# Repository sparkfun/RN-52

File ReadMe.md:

SparkFun RN-52 Audio Bluetooth Breakout
=======================================

[*SparkFun RN-52 Breakout (WRL-12849)*](https://www.sparkfun.com/products/12849)

This RN-52 Bluetooth from Roving Network is an audio module that provides a highly integrated solution for delivering high quality stereo audio in a small form factor with little difficulty.

Repository Contents
-------------------
* **/Hardware** - Eagle PCB layout files
* **/Production** - Test bed files and production panel files

Product Versions
----------------
* [WRL-12849](https://www.sparkfun.com/products/12849)- Version 1.1. Currently for sale. 
* [WRL-11777](https://www.sparkfun.com/products/retired/11777)- Version 1.0. Retired. 

Version History
---------------
* [v11](https://github.com/sparkfun/RN-52/tree/V_11) GitHub version 1.1. Current version. 
* [v10](https://github.com/sparkfun/RN-52/tree/V_10) GitHub version 1.0. Retired.

License Information
-------------------
The hardware is released under [Creative Commons ShareAlike 4.0 International](https://creativecommons.org/licenses/by-sa/4.0/).

Distributed as-is; no warranty is given.

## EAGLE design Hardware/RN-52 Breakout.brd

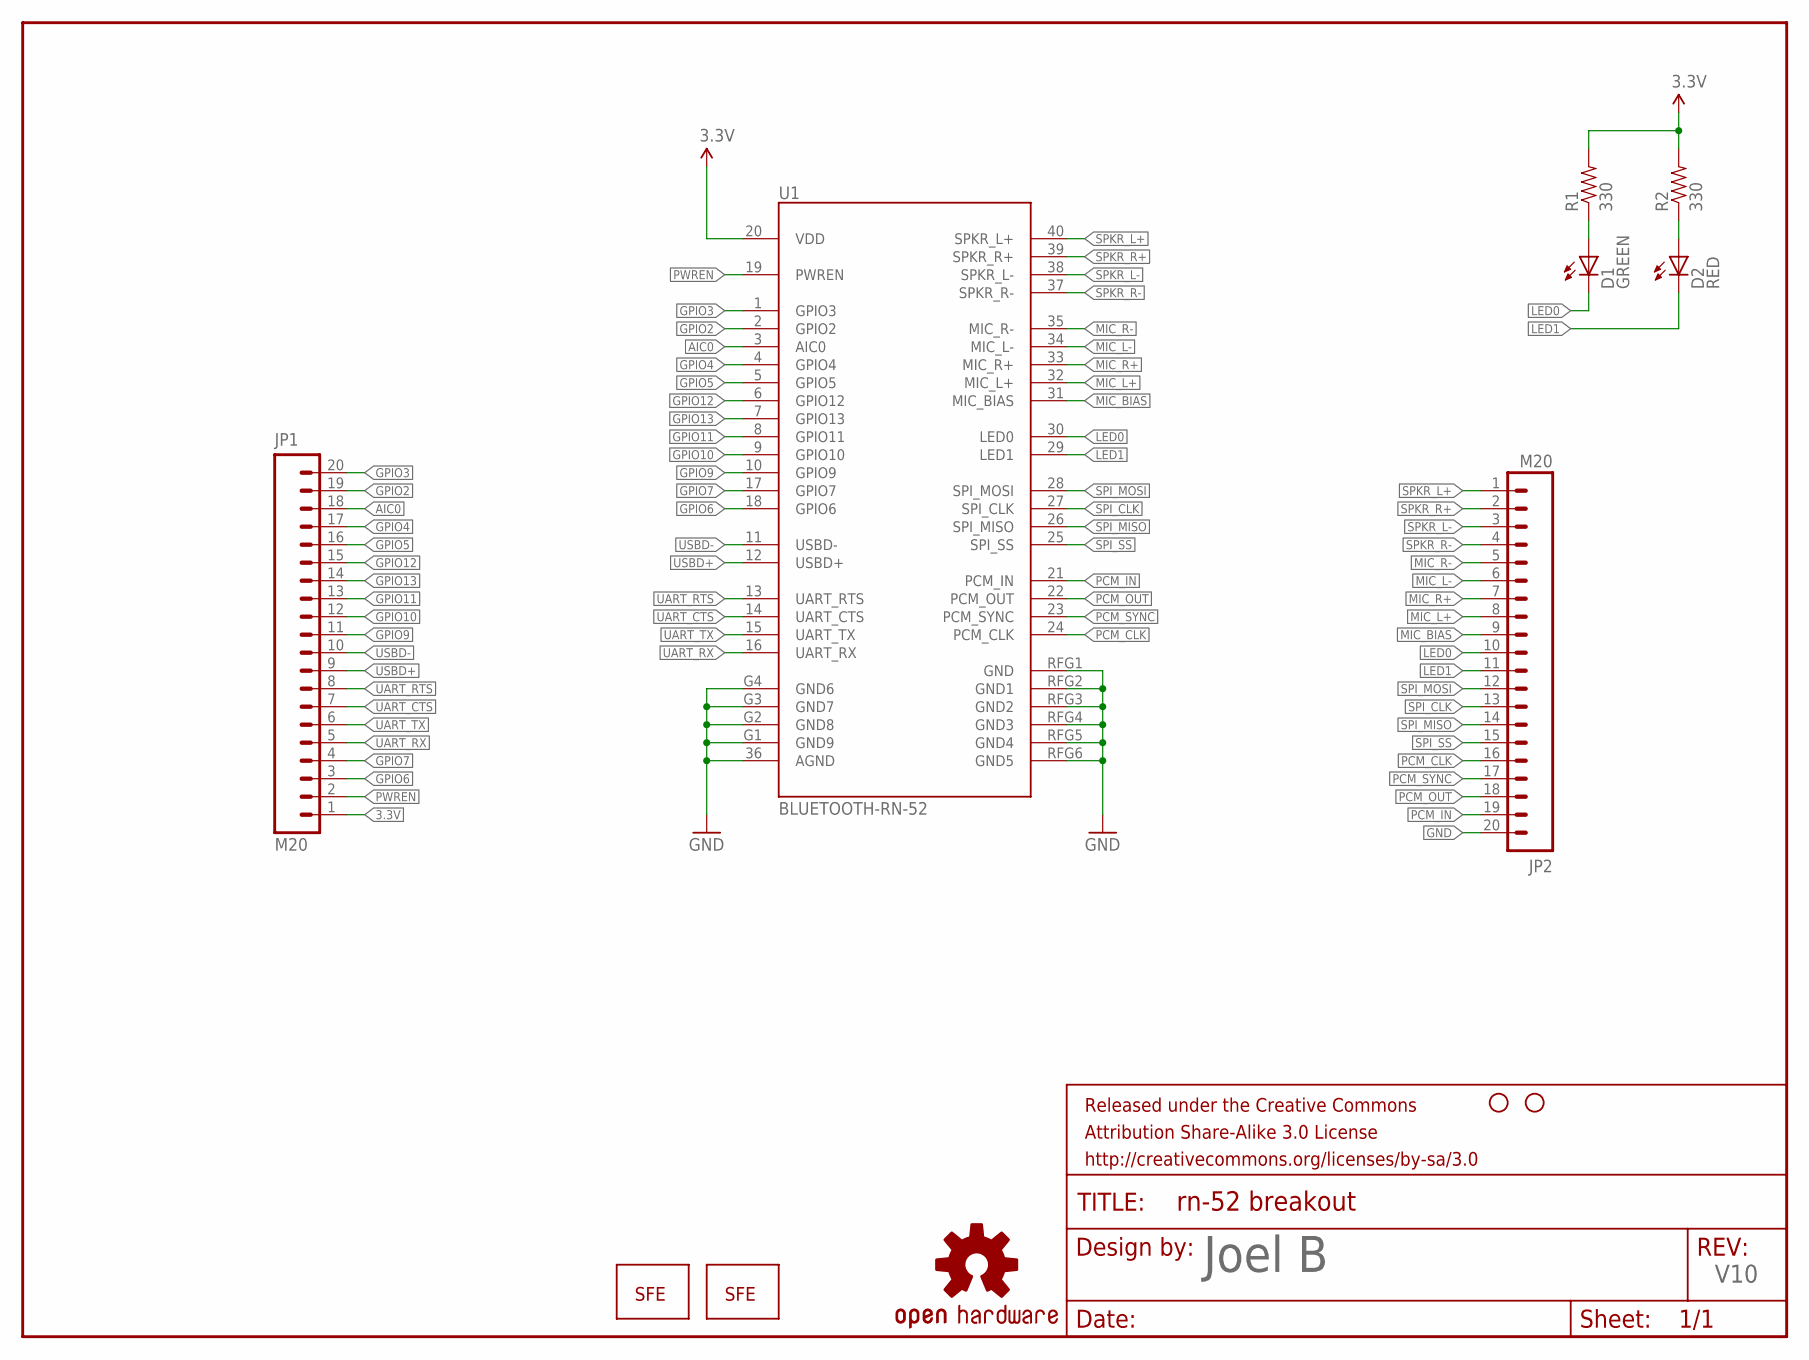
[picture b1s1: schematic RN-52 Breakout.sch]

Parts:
D1: GREEN; LED-0603
D2: RED; LED-0603
FRAME1: FRAME-LETTER; CREATIVE_COMMONS
JP1, JP2: M20; 1X20
LOGO1: OSHW-LOGOS; OSHW-LOGO-S
LOGO3: LOGO-SFENEW; SFE-NEW-WEBLOGO
LOGO4: LOGO-SFENW2; SFE-NEW-WEB
R1, R2: 330; 0603-RES
STANDOFF1, STANDOFF2: STAND-OFF
U1: BLUETOOTH-RN-52; RN-52

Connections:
3.3V: JP1.1, R1.2, R2.2, U1.20 (VDD)
AIC0: JP1.18, U1.3 (AIC0)
GND: JP2.20, U1.36 (AGND), U1.G1 (GND9), U1.G2 (GND8), U1.G3 (GND7), U1.G4 (GND6), U1.RFG1 (GND), U1.RFG2 (GND1), U1.RFG3 (GND2), U1.RFG4 (GND3), U1.RFG5 (GND4), U1.RFG6 (GND5)
GPIO2: JP1.19, U1.2 (GPIO2)
GPIO3: JP1.20, U1.1 (GPIO3)
GPIO4: JP1.17, U1.4 (GPIO4)
GPIO5: JP1.16, U1.5 (GPIO5)
GPIO6: JP1.3, U1.18 (GPIO6)
GPIO7: JP1.4, U1.17 (GPIO7)
GPIO9: JP1.11, U1.10 (GPIO9)
GPIO10: JP1.12, U1.9 (GPIO10)
GPIO11: JP1.13, U1.8 (GPIO11)
GPIO12: JP1.15, U1.6 (GPIO12)
GPIO13: JP1.14, U1.7 (GPIO13)
LED0: D1.C, JP2.10, U1.30 (LED0)
LED1: D2.C, JP2.11, U1.29 (LED1)
MIC_BIAS: JP2.9, U1.31 (MIC_BIAS)
MIC_L+: JP2.8, U1.32 (MIC_L+)
MIC_L-: JP2.6, U1.34 (MIC_L-)
MIC_R+: JP2.7, U1.33 (MIC_R+)
MIC_R-: JP2.5, U1.35 (MIC_R-)
unnamed: D2.A, R2.1
unnamed: D1.A, R1.1
PCM_CLK: JP2.16, U1.24 (PCM_CLK)
PCM_IN: JP2.19, U1.21 (PCM_IN)
PCM_OUT: JP2.18, U1.22 (PCM_OUT)
PCM_SYNC: JP2.17, U1.23 (PCM_SYNC)
PWREN: JP1.2, U1.19 (PWREN)
SPI_CLK: JP2.13, U1.27 (SPI_CLK)
SPI_MISO: JP2.14, U1.26 (SPI_MISO)
SPI_MOSI: JP2.12, U1.28 (SPI_MOSI)
SPI_SS: JP2.15, U1.25 (SPI_SS)
SPKR_L+: JP2.1, U1.40 (SPKR_L+)
SPKR_L-: JP2.3, U1.38 (SPKR_L-)
SPKR_R+: JP2.2, U1.39 (SPKR_R+)
SPKR_R-: JP2.4, U1.37 (SPKR_R-)
UART_CTS: JP1.7, U1.14 (UART_CTS)
UART_RTS: JP1.8, U1.13 (UART_RTS)
UART_RX: JP1.5, U1.16 (UART_RX)
UART_TX: JP1.6, U1.15 (UART_TX)
USBD+: JP1.9, U1.12 (USBD+)
USBD-: JP1.10, U1.11 (USBD-)

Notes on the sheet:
Joel B
V10

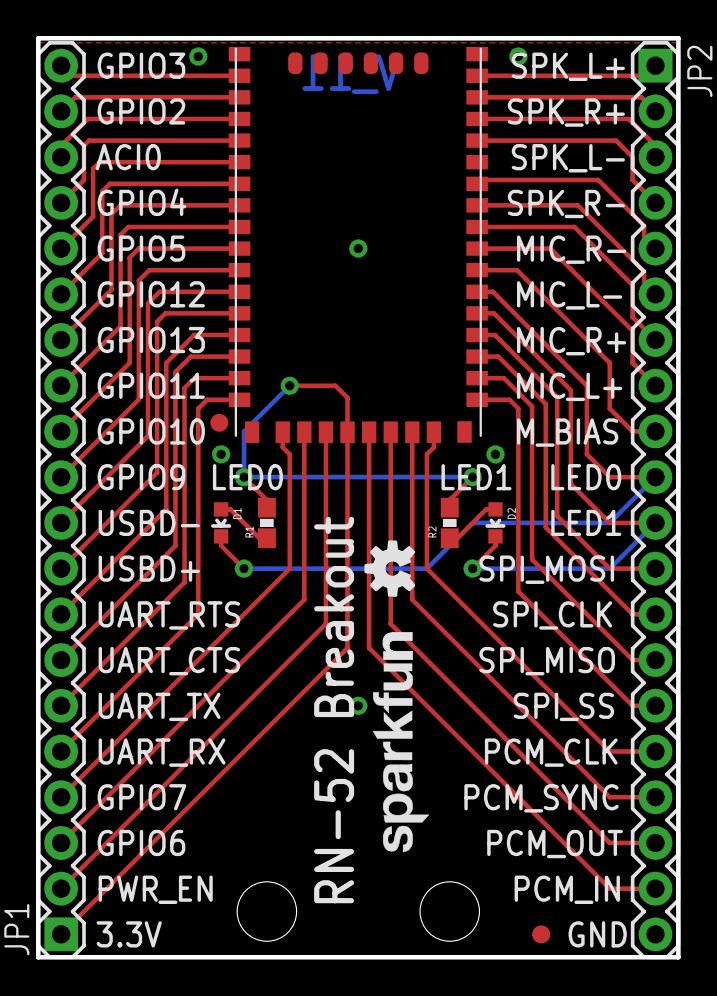
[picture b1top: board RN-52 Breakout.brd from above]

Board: 2 copper layers, 35.6 x 51.1 mm, 15 parts (1 on the bottom side), 42 nets.

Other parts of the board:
FID1, FID2: FIDUCIAL1X2; FIDUCIAL-1X2

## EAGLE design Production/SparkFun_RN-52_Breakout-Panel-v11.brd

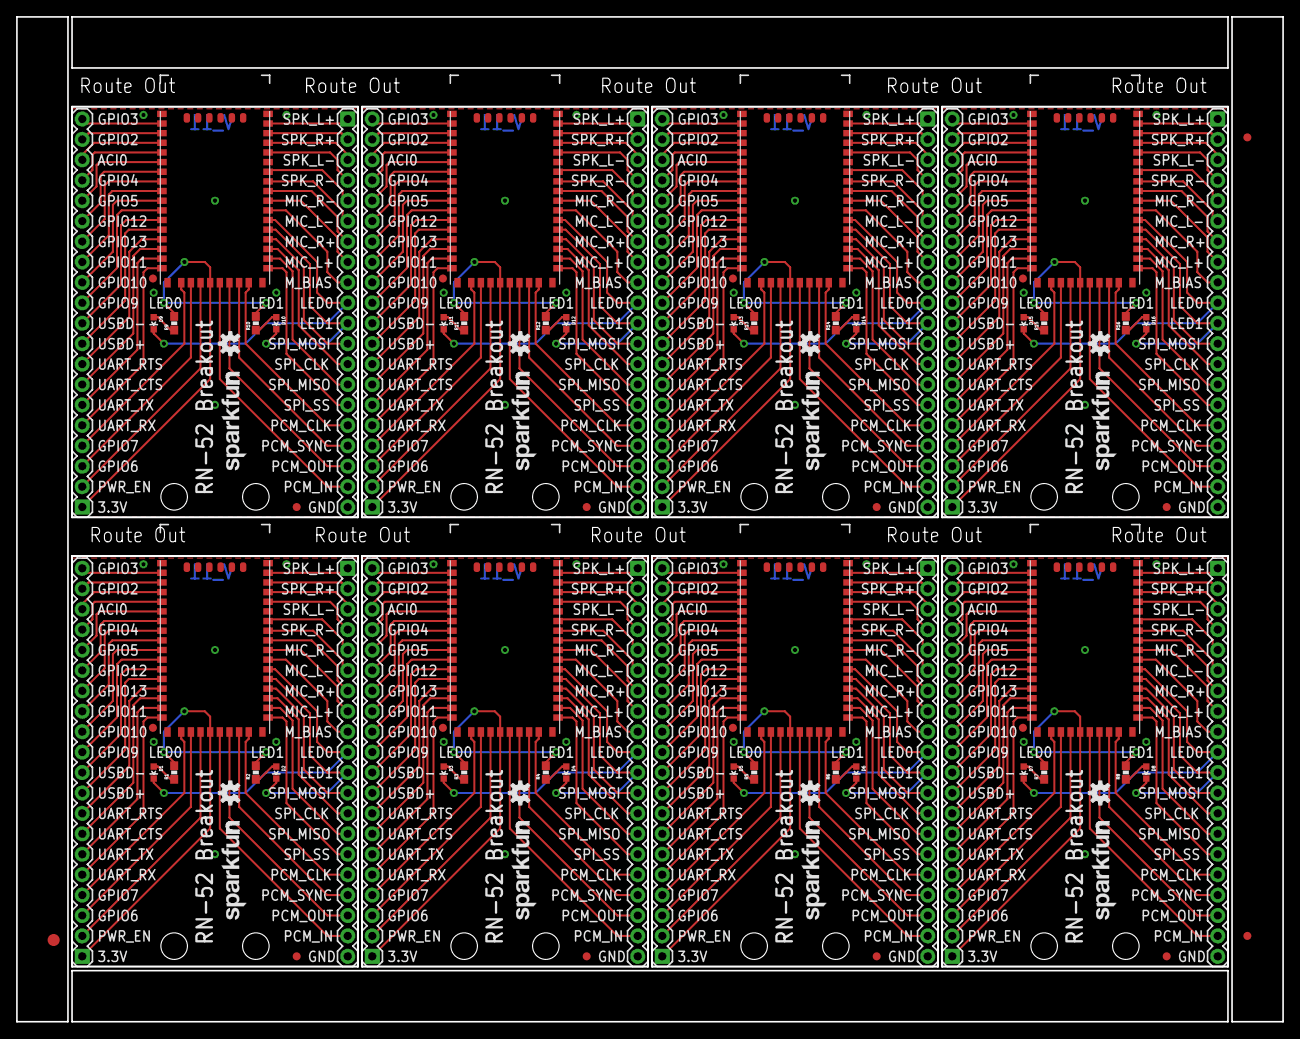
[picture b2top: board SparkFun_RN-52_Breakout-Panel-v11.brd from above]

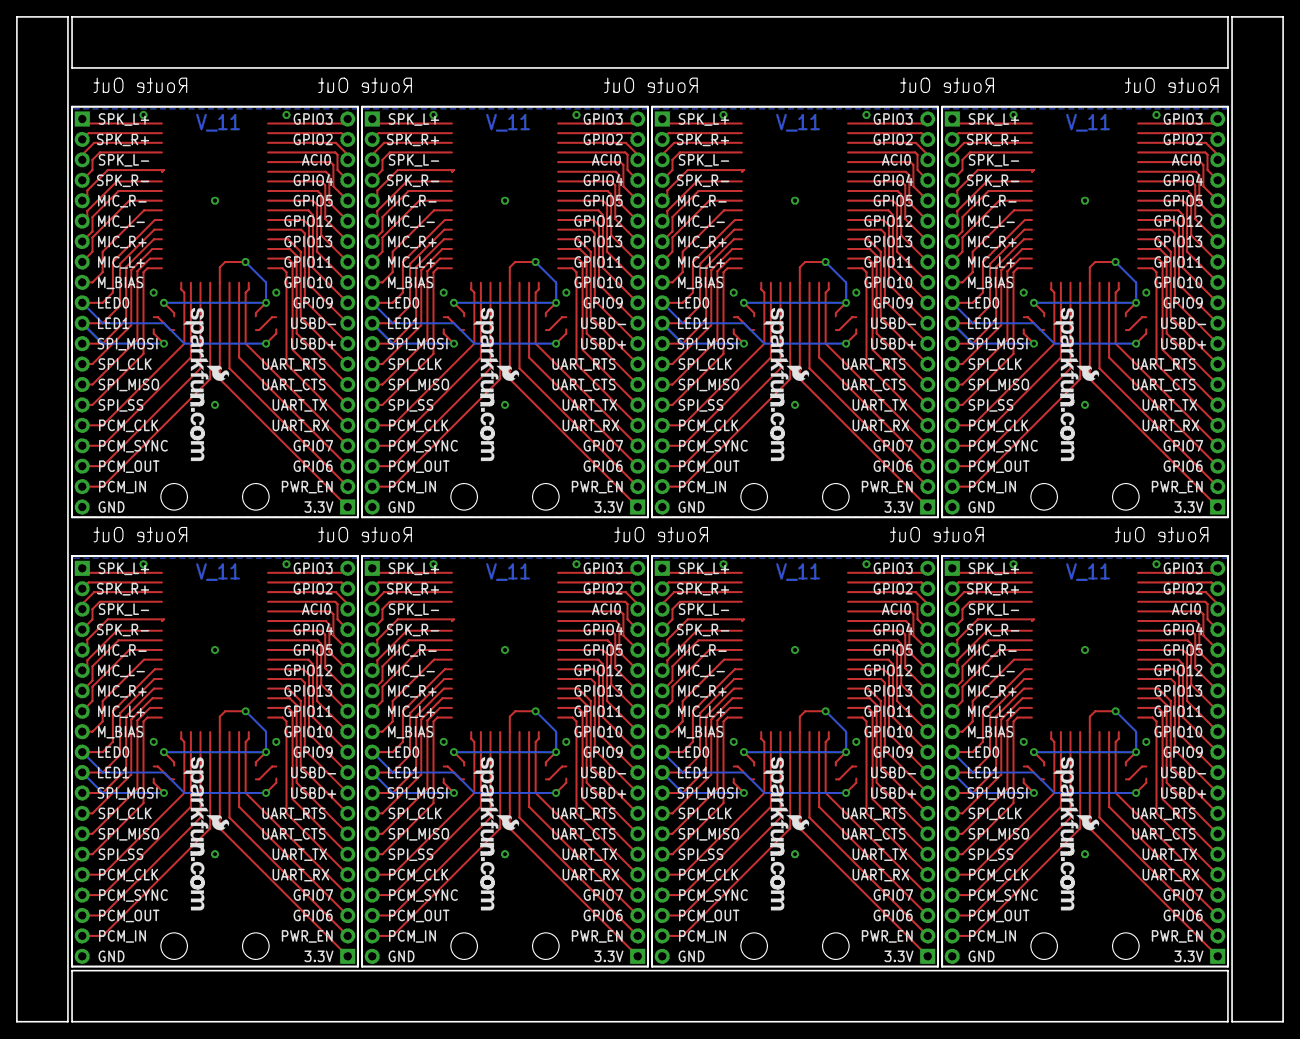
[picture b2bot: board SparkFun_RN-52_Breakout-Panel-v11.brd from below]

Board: 2 copper layers, 157.5 x 125.0 mm, 115 parts (8 on the bottom side), 336 nets.

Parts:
D1, D3, D5, D7, D9, D11, D13, D15: GREEN; LED-0603
D2, D4, D6, D8, D10, D12, D14, D16: RED; LED-0603
E$1: FIDUCIAL-1.5X3
E$3, E$8: FIDUCIAL-1X2
FID1, FID2, FID3, FID4, FID5, FID6, FID7, FID8, FID9, FID10, FID11, FID12, FID13, FID14, FID15, FID16: FIDUCIAL1X2; FIDUCIAL-1X2
JP1, JP2, JP3, JP4, JP5, JP6, JP7, JP8, JP9, JP10, JP11, JP12, JP13, JP14, JP15, JP16: M20; 1X20
LOGO1, LOGO2, LOGO7, LOGO10, LOGO13, LOGO16, LOGO19, LOGO22: OSHW-LOGOS; OSHW-LOGO-S
LOGO3, LOGO5, LOGO8, LOGO11, LOGO14, LOGO17, LOGO20, LOGO23: LOGO-SFENEW; SFE-NEW-WEBLOGO
LOGO4, LOGO6, LOGO9, LOGO12, LOGO15, LOGO18, LOGO21, LOGO24: LOGO-SFENW2; SFE-NEW-WEB
R1, R2, R3, R4, R5, R6, R7, R8, R9, R10, R11, R12, R13, R14, R15, R16: 330; 0603-RES
STANDOFF1, STANDOFF2, STANDOFF3, STANDOFF4, STANDOFF5, STANDOFF6, STANDOFF7, STANDOFF8, STANDOFF9, STANDOFF10, STANDOFF11, STANDOFF12, STANDOFF13, STANDOFF14, STANDOFF15, STANDOFF16: STAND-OFF
U1, U2, U3, U4, U5, U6, U7, U8: BLUETOOTH-RN-52; RN-52

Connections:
3.3V: JP1.1, R1.2, R2.2, U1.20
3.3V1: JP3.1, R3.2, R4.2, U2.20
3.3V2: JP5.1, R5.2, R6.2, U3.20
3.3V3: JP7.1, R7.2, R8.2, U4.20
3.3V4: JP9.1, R9.2, R10.2, U5.20
3.3V5: JP11.1, R11.2, R12.2, U6.20
3.3V6: JP13.1, R13.2, R14.2, U7.20
3.3V7: JP15.1, R15.2, R16.2, U8.20
AIC0: JP1.18, U1.3
AIC1: JP3.18, U2.3
AIC2: JP5.18, U3.3
AIC3: JP7.18, U4.3
AIC4: JP9.18, U5.3
AIC5: JP11.18, U6.3
AIC6: JP13.18, U7.3
AIC7: JP15.18, U8.3
GND: JP2.20, U1.36, U1.G1, U1.G2, U1.G3, U1.G4, U1.RFG1, U1.RFG2, U1.RFG3, U1.RFG4, U1.RFG5, U1.RFG6
GND1: JP4.20, U2.36, U2.G1, U2.G2, U2.G3, U2.G4, U2.RFG1, U2.RFG2, U2.RFG3, U2.RFG4, U2.RFG5, U2.RFG6
GND2: JP6.20, U3.36, U3.G1, U3.G2, U3.G3, U3.G4, U3.RFG1, U3.RFG2, U3.RFG3, U3.RFG4, U3.RFG5, U3.RFG6
GND3: JP8.20, U4.36, U4.G1, U4.G2, U4.G3, U4.G4, U4.RFG1, U4.RFG2, U4.RFG3, U4.RFG4, U4.RFG5, U4.RFG6
GND4: JP10.20, U5.36, U5.G1, U5.G2, U5.G3, U5.G4, U5.RFG1, U5.RFG2, U5.RFG3, U5.RFG4, U5.RFG5, U5.RFG6
GND5: JP12.20, U6.36, U6.G1, U6.G2, U6.G3, U6.G4, U6.RFG1, U6.RFG2, U6.RFG3, U6.RFG4, U6.RFG5, U6.RFG6
GND6: JP14.20, U7.36, U7.G1, U7.G2, U7.G3, U7.G4, U7.RFG1, U7.RFG2, U7.RFG3, U7.RFG4, U7.RFG5, U7.RFG6
GND7: JP16.20, U8.36, U8.G1, U8.G2, U8.G3, U8.G4, U8.RFG1, U8.RFG2, U8.RFG3, U8.RFG4, U8.RFG5, U8.RFG6
GPIO1: JP3.20, U2.1
GPIO2: JP1.19, U1.2
GPIO3: JP1.20, U1.1
GPIO4: JP1.17, U1.4
GPIO5: JP1.16, U1.5
GPIO6: JP1.3, U1.18
GPIO7: JP1.4, U1.17
GPIO8: JP3.19, U2.2
GPIO9: JP1.11, U1.10
GPIO10: JP1.12, U1.9
GPIO11: JP1.13, U1.8
GPIO12: JP1.15, U1.6
GPIO13: JP1.14, U1.7
GPIO14: JP3.17, U2.4
GPIO15: JP3.16, U2.5
GPIO16: JP3.15, U2.6
GPIO17: JP3.14, U2.7
GPIO18: JP3.13, U2.8
GPIO19: JP3.12, U2.9
GPIO20: JP3.11, U2.10
GPIO21: JP3.4, U2.17
GPIO22: JP3.3, U2.18
GPIO23: JP5.20, U3.1
GPIO24: JP5.19, U3.2
GPIO25: JP5.17, U3.4
GPIO26: JP5.16, U3.5
GPIO27: JP5.15, U3.6
GPIO28: JP5.14, U3.7
GPIO29: JP5.13, U3.8
GPIO30: JP5.12, U3.9
GPIO31: JP5.11, U3.10
GPIO32: JP5.4, U3.17
GPIO33: JP5.3, U3.18
GPIO34: JP7.20, U4.1
GPIO35: JP7.19, U4.2
GPIO36: JP7.17, U4.4
GPIO37: JP7.16, U4.5
GPIO38: JP7.15, U4.6
GPIO39: JP7.14, U4.7
GPIO40: JP7.13, U4.8
GPIO41: JP7.12, U4.9
GPIO42: JP7.11, U4.10
GPIO43: JP7.4, U4.17
GPIO44: JP7.3, U4.18
GPIO45: JP9.20, U5.1
GPIO46: JP9.19, U5.2
GPIO47: JP9.17, U5.4
GPIO48: JP9.16, U5.5
GPIO49: JP9.15, U5.6
GPIO50: JP9.14, U5.7
GPIO51: JP9.13, U5.8
GPIO52: JP9.12, U5.9
GPIO53: JP9.11, U5.10
GPIO54: JP9.4, U5.17
GPIO55: JP9.3, U5.18
GPIO56: JP11.20, U6.1
GPIO57: JP11.19, U6.2
GPIO58: JP11.17, U6.4
GPIO59: JP11.16, U6.5
GPIO60: JP11.15, U6.6
GPIO61: JP11.14, U6.7
GPIO62: JP11.13, U6.8
GPIO63: JP11.12, U6.9
GPIO64: JP11.11, U6.10
GPIO65: JP11.4, U6.17
GPIO66: JP11.3, U6.18
GPIO67: JP13.20, U7.1
GPIO68: JP13.19, U7.2
GPIO69: JP13.17, U7.4
GPIO70: JP13.16, U7.5
GPIO71: JP13.15, U7.6
GPIO72: JP13.14, U7.7
GPIO73: JP13.13, U7.8
GPIO74: JP13.12, U7.9
GPIO75: JP13.11, U7.10
GPIO76: JP13.4, U7.17
GPIO77: JP13.3, U7.18
GPIO78: JP15.20, U8.1
GPIO79: JP15.19, U8.2
GPIO80: JP15.17, U8.4
GPIO81: JP15.16, U8.5
GPIO82: JP15.15, U8.6
GPIO83: JP15.14, U8.7
GPIO84: JP15.13, U8.8
GPIO85: JP15.12, U8.9
GPIO86: JP15.11, U8.10
GPIO87: JP15.4, U8.17
GPIO88: JP15.3, U8.18
LED0: D1.C, JP2.10, U1.30
LED1: D2.C, JP2.11, U1.29
LED2: D3.C, JP4.10, U2.30
LED3: D4.C, JP4.11, U2.29
LED4: D5.C, JP6.10, U3.30
LED5: D6.C, JP6.11, U3.29
LED6: D7.C, JP8.10, U4.30
LED7: D8.C, JP8.11, U4.29
LED8: D9.C, JP10.10, U5.30
LED9: D10.C, JP10.11, U5.29
LED10: D11.C, JP12.10, U6.30
LED11: D12.C, JP12.11, U6.29
LED12: D13.C, JP14.10, U7.30
LED13: D14.C, JP14.11, U7.29
LED14: D15.C, JP16.10, U8.30
LED15: D16.C, JP16.11, U8.29
MIC_BIAS: JP2.9, U1.31
MIC_BIAS1: JP4.9, U2.31
MIC_BIAS2: JP6.9, U3.31
MIC_BIAS3: JP8.9, U4.31
MIC_BIAS4: JP10.9, U5.31
MIC_BIAS5: JP12.9, U6.31
MIC_BIAS6: JP14.9, U7.31
MIC_BIAS7: JP16.9, U8.31
MIC_L+: JP2.8, U1.32
MIC_L+1: JP4.8, U2.32
MIC_L+2: JP6.8, U3.32
MIC_L+3: JP8.8, U4.32
MIC_L+4: JP10.8, U5.32
MIC_L+5: JP12.8, U6.32
MIC_L+6: JP14.8, U7.32
MIC_L+7: JP16.8, U8.32
MIC_L-: JP2.6, U1.34
MIC_L-1: JP4.6, U2.34
MIC_L-2: JP6.6, U3.34
MIC_L-3: JP8.6, U4.34
MIC_L-4: JP10.6, U5.34
MIC_L-5: JP12.6, U6.34
MIC_L-6: JP14.6, U7.34
MIC_L-7: JP16.6, U8.34
MIC_R+: JP2.7, U1.33
MIC_R+1: JP4.7, U2.33
MIC_R+2: JP6.7, U3.33
MIC_R+3: JP8.7, U4.33
MIC_R+4: JP10.7, U5.33
MIC_R+5: JP12.7, U6.33
MIC_R+6: JP14.7, U7.33
MIC_R+7: JP16.7, U8.33
MIC_R-: JP2.5, U1.35
MIC_R-1: JP4.5, U2.35
MIC_R-2: JP6.5, U3.35
MIC_R-3: JP8.5, U4.35
MIC_R-4: JP10.5, U5.35
MIC_R-5: JP12.5, U6.35
MIC_R-6: JP14.5, U7.35
MIC_R-7: JP16.5, U8.35
unnamed: D2.A, R2.1
unnamed: D1.A, R1.1
unnamed: D4.A, R4.1
unnamed: D3.A, R3.1
unnamed: D6.A, R6.1
unnamed: D5.A, R5.1
unnamed: D8.A, R8.1
unnamed: D7.A, R7.1
unnamed: D10.A, R10.1
unnamed: D9.A, R9.1
unnamed: D12.A, R12.1
unnamed: D11.A, R11.1
unnamed: D14.A, R14.1
unnamed: D13.A, R13.1
unnamed: D16.A, R16.1
unnamed: D15.A, R15.1
PCM_CLK: JP2.16, U1.24
PCM_CLK1: JP4.16, U2.24
PCM_CLK2: JP6.16, U3.24
PCM_CLK3: JP8.16, U4.24
PCM_CLK4: JP10.16, U5.24
PCM_CLK5: JP12.16, U6.24
PCM_CLK6: JP14.16, U7.24
PCM_CLK7: JP16.16, U8.24
PCM_IN: JP2.19, U1.21
PCM_IN1: JP4.19, U2.21
PCM_IN2: JP6.19, U3.21
PCM_IN3: JP8.19, U4.21
PCM_IN4: JP10.19, U5.21
PCM_IN5: JP12.19, U6.21
PCM_IN6: JP14.19, U7.21
PCM_IN7: JP16.19, U8.21
PCM_OUT: JP2.18, U1.22
PCM_OUT1: JP4.18, U2.22
PCM_OUT2: JP6.18, U3.22
PCM_OUT3: JP8.18, U4.22
PCM_OUT4: JP10.18, U5.22
PCM_OUT5: JP12.18, U6.22
PCM_OUT6: JP14.18, U7.22
PCM_OUT7: JP16.18, U8.22
PCM_SYNC: JP2.17, U1.23
PCM_SYNC1: JP4.17, U2.23
PCM_SYNC2: JP6.17, U3.23
PCM_SYNC3: JP8.17, U4.23
PCM_SYNC4: JP10.17, U5.23
PCM_SYNC5: JP12.17, U6.23
PCM_SYNC6: JP14.17, U7.23
PCM_SYNC7: JP16.17, U8.23
PWREN: JP1.2, U1.19
PWREN1: JP3.2, U2.19
PWREN2: JP5.2, U3.19
PWREN3: JP7.2, U4.19
PWREN4: JP9.2, U5.19
PWREN5: JP11.2, U6.19
PWREN6: JP13.2, U7.19
PWREN7: JP15.2, U8.19
SPI_CLK: JP2.13, U1.27
SPI_CLK1: JP4.13, U2.27
SPI_CLK2: JP6.13, U3.27
SPI_CLK3: JP8.13, U4.27
SPI_CLK4: JP10.13, U5.27
SPI_CLK5: JP12.13, U6.27
SPI_CLK6: JP14.13, U7.27
SPI_CLK7: JP16.13, U8.27
SPI_MISO: JP2.14, U1.26
SPI_MISO1: JP4.14, U2.26
SPI_MISO2: JP6.14, U3.26
SPI_MISO3: JP8.14, U4.26
SPI_MISO4: JP10.14, U5.26
SPI_MISO5: JP12.14, U6.26
SPI_MISO6: JP14.14, U7.26
SPI_MISO7: JP16.14, U8.26
SPI_MOSI: JP2.12, U1.28
SPI_MOSI1: JP4.12, U2.28
SPI_MOSI2: JP6.12, U3.28
SPI_MOSI3: JP8.12, U4.28
SPI_MOSI4: JP10.12, U5.28
SPI_MOSI5: JP12.12, U6.28
SPI_MOSI6: JP14.12, U7.28
SPI_MOSI7: JP16.12, U8.28
SPI_SS: JP2.15, U1.25
SPI_SS1: JP4.15, U2.25
SPI_SS2: JP6.15, U3.25
SPI_SS3: JP8.15, U4.25
SPI_SS4: JP10.15, U5.25
SPI_SS5: JP12.15, U6.25
SPI_SS6: JP14.15, U7.25
SPI_SS7: JP16.15, U8.25
SPKR_L+: JP2.1, U1.40
SPKR_L+1: JP4.1, U2.40
SPKR_L+2: JP6.1, U3.40
SPKR_L+3: JP8.1, U4.40
SPKR_L+4: JP10.1, U5.40
SPKR_L+5: JP12.1, U6.40
SPKR_L+6: JP14.1, U7.40
SPKR_L+7: JP16.1, U8.40
SPKR_L-: JP2.3, U1.38
SPKR_L-1: JP4.3, U2.38
SPKR_L-2: JP6.3, U3.38
SPKR_L-3: JP8.3, U4.38
SPKR_L-4: JP10.3, U5.38
SPKR_L-5: JP12.3, U6.38
SPKR_L-6: JP14.3, U7.38
SPKR_L-7: JP16.3, U8.38
SPKR_R+: JP2.2, U1.39
SPKR_R+1: JP4.2, U2.39
SPKR_R+2: JP6.2, U3.39
SPKR_R+3: JP8.2, U4.39
SPKR_R+4: JP10.2, U5.39
SPKR_R+5: JP12.2, U6.39
SPKR_R+6: JP14.2, U7.39
SPKR_R+7: JP16.2, U8.39
SPKR_R-: JP2.4, U1.37
SPKR_R-1: JP4.4, U2.37
SPKR_R-2: JP6.4, U3.37
SPKR_R-3: JP8.4, U4.37
SPKR_R-4: JP10.4, U5.37
SPKR_R-5: JP12.4, U6.37
SPKR_R-6: JP14.4, U7.37
SPKR_R-7: JP16.4, U8.37
UART_CTS: JP1.7, U1.14
UART_CTS1: JP3.7, U2.14
UART_CTS2: JP5.7, U3.14
UART_CTS3: JP7.7, U4.14
UART_CTS4: JP9.7, U5.14
UART_CTS5: JP11.7, U6.14
UART_CTS6: JP13.7, U7.14
UART_CTS7: JP15.7, U8.14
UART_RTS: JP1.8, U1.13
UART_RTS1: JP3.8, U2.13
UART_RTS2: JP5.8, U3.13
UART_RTS3: JP7.8, U4.13
UART_RTS4: JP9.8, U5.13
UART_RTS5: JP11.8, U6.13
UART_RTS6: JP13.8, U7.13
UART_RTS7: JP15.8, U8.13
UART_RX: JP1.5, U1.16
UART_RX1: JP3.5, U2.16
UART_RX2: JP5.5, U3.16
UART_RX3: JP7.5, U4.16
UART_RX4: JP9.5, U5.16
UART_RX5: JP11.5, U6.16
UART_RX6: JP13.5, U7.16
UART_RX7: JP15.5, U8.16
UART_TX: JP1.6, U1.15
UART_TX1: JP3.6, U2.15
UART_TX2: JP5.6, U3.15
UART_TX3: JP7.6, U4.15
UART_TX4: JP9.6, U5.15
UART_TX5: JP11.6, U6.15
UART_TX6: JP13.6, U7.15
UART_TX7: JP15.6, U8.15
USBD+: JP1.9, U1.12
USBD+1: JP3.9, U2.12
USBD+2: JP5.9, U3.12
USBD+3: JP7.9, U4.12
USBD+4: JP9.9, U5.12
USBD+5: JP11.9, U6.12
USBD+6: JP13.9, U7.12
USBD+7: JP15.9, U8.12
USBD-: JP1.10, U1.11
USBD-1: JP3.10, U2.11
USBD-2: JP5.10, U3.11
USBD-3: JP7.10, U4.11
USBD-4: JP9.10, U5.11
USBD-5: JP11.10, U6.11
USBD-6: JP13.10, U7.11
USBD-7: JP15.10, U8.11

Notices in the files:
parts and their libraries:
SparkFun-RF: Licensing: CC v3.0 Share-Alike You are welcome to use this library for commercial purposes.
SparkFun-Aesthetics: Released under the Creative Commons Attribution Share-Alike 3.0 License
SparkFun-Aesthetics: http://creativecommons.org/licenses/by-sa/3.0
